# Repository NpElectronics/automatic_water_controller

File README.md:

# Automatic Motor Controller

## Software Required
+ [Eagle](https://www.autodesk.com/products/eagle/overview)
+ Library for eagle - [adafruit](https://github.com/adafruit/Adafruit-Eagle-Library)

## Hardware Required:

### Power Circuit:

+ Diode, 1n4007 -4x
+ Zenor DIode, 6v2 - 1x
+ Capacitor Electrolytic, 100uF -1x
+ X-Rated Capacitor, 1x
+ Resistor, 2M2 -1x
+ Voltage Regulator, 7805 -1x
+ Terminal Block, 2pin -1x
+ Male header block, 3pin -1x
+ Prototype matrix board, small -1x

### Controller Board:
+ Male Header(Box), 4pin -1x
+ Male Header(Box), 3pin, 2x
+ Nand Gate, 7400 -2x
+ JK flipflop, 74HC76N -1x
+ Transistor, BC548 -1x
+ Resisotor, 1k, 1x
+ Diode, 1n4007 - 1x
+ Electrolytic capacitor, 470uF - 1x 
+ Electromechanical Relay, 6V -1x

## Cost Estimation
+ x-rated Capacitor Rs.45
+ Resistor 2M2      Rs.5
+ Other power circuit Rs.140

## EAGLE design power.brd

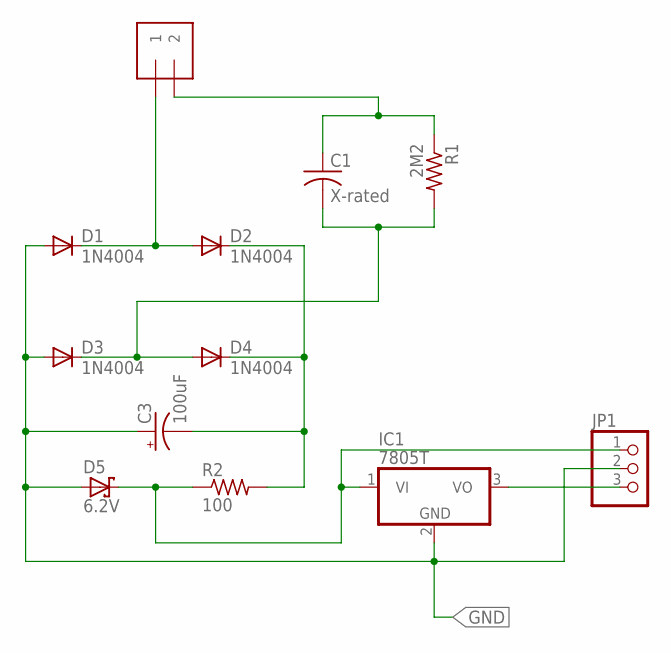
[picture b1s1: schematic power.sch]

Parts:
C1: X-rated; C225-108X268
C3: 100uF; E2,5-5; MPN ECA-1EHG101
D1, D2, D3, D4: 1N4004; DO41-10; MPN 1N4007RLG
D5: 6.2V; DO41-7; MPN 1N823A
IC1: 7805T; TO220H; MPN KA7805AETU
J1: 1X2-3.5MM
JP1: PINHD-1X3CB; 1X03-CLEANBIG
R1: 2M2; 0207/10; MPN CRCW08052M20JNEA
R2: 100; 0207/10; MPN 25J100E

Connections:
GND: C3.+, D1.A, D3.A, D5.A, IC1.2 (GND), JP1.2
unnamed: D1.C, D2.A, J1.1
unnamed: C3.-, D2.C, D4.C, R2.2
unnamed: C1.2, D3.C, D4.A, R1.2
unnamed: C1.1, J1.2, R1.1
unnamed: D5.C, IC1.1 (VI), JP1.1, R2.1
unnamed: IC1.3 (VO), JP1.3

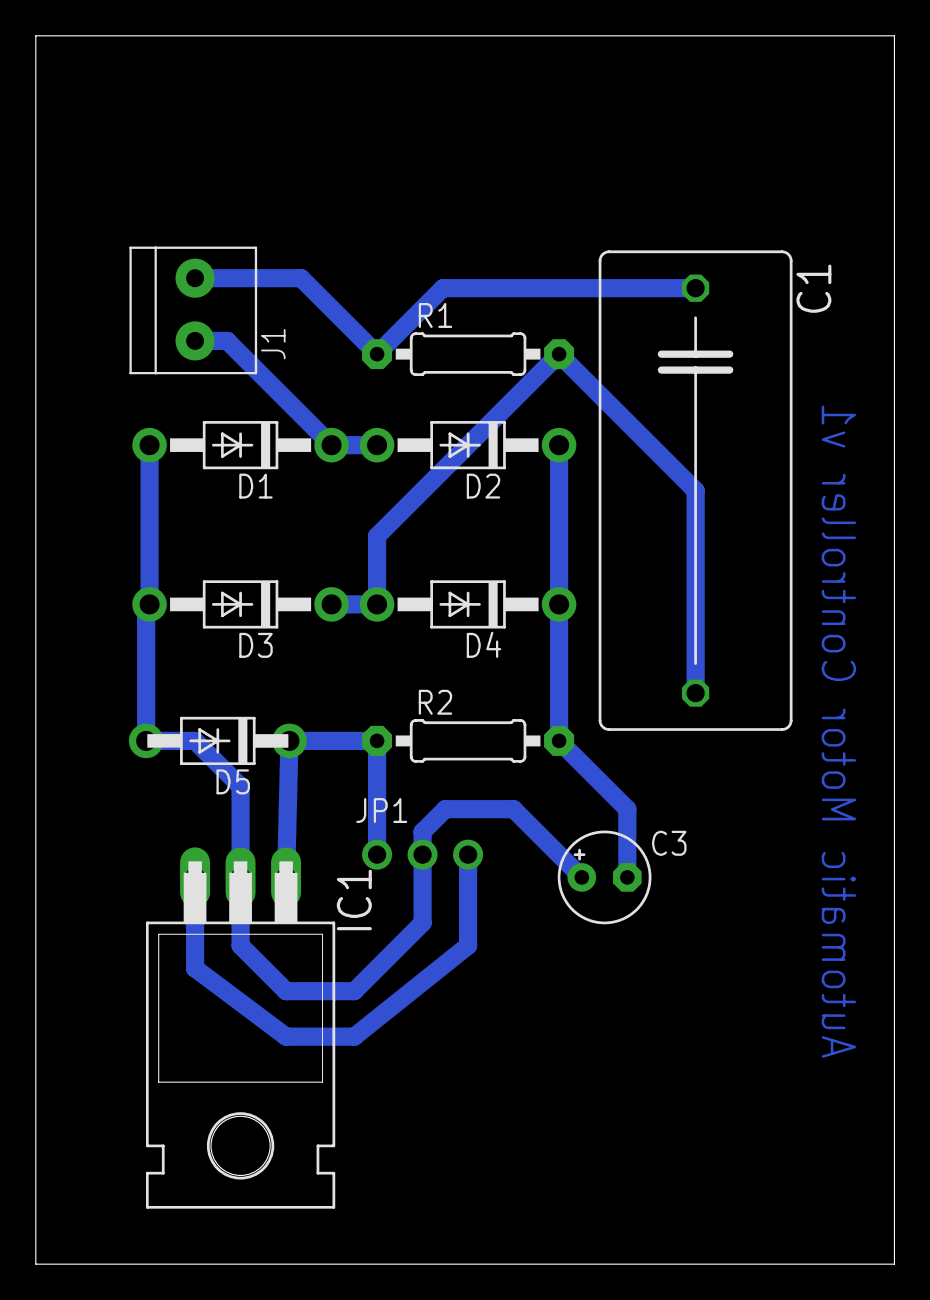
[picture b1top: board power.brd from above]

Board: 2 copper layers, 47.9 x 68.6 mm, 12 parts (0 on the bottom side), 7 nets.

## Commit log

2017-06-18 Add docs folder
2017-06-18 Update README.md
    Add software requirement
2017-06-18 Format file
    Use hardware requirement one time instead of 2
2017-06-18 Add power schematic figure
2017-06-18 Update README.md
    I have add the cost estimation in the file
